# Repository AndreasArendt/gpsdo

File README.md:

# GPSDO

**GPSDO** (GPS Disciplined Oscillator) combines the precision of a high-quality OCXO (Oven-Controlled Crystal Oscillator) with the pulse-per-second (PPS) signal from a GNSS receiver. The goal is to achieve accurate time and frequency reference, down to the nanosecond level.

This project aims to create an **open-source and affordable** GPSDO from scratch, including designing custom hardware (PCB) and developing the supporting software.

# Features
* Combines GNSS PPS with a high-precision OCXO
* Fully open-source hardware and software
* Targeting nanosecond-level timing precision
* Modular design for hardware and software development

# Status
🚧 Under Construction
* The first hardware prototype is currently being tested; all findings are documented in Issue #1
* A Kalman-Filter to estimate `phase`, `frequency_offset` and `frequency_drift` has been implemented
* A PI-Controller is running the GPSDO closed loop
* Flatbuf Messages are implemented to ensure easy-to-extend communication to a host system

# Roadmap
✅ Improve hardware based on findings from V2 prototype  
🔄 Integrate the GNSS receiver on-board for a fully standalone GPSDO  
⚙️ Fine-tune the control loop and filtering algorithms  
📊 Benchmark the true performance against reference standards  

# Contributing
Contributions are welcome! Whether it's hardware design suggestions, software improvements, or analysis scripts, feel free to open an issue or a pull request.

## Compiling flatcc (Windows)
* Navigate into `flatcc` submodule folder.  
* Create `build` folder
* Navigate into `build` folder
* Run `cmake ..`
* Run `cmake --build . --config Release`
* Executable is in `flatcc/bin/Release/flatcc.exe`

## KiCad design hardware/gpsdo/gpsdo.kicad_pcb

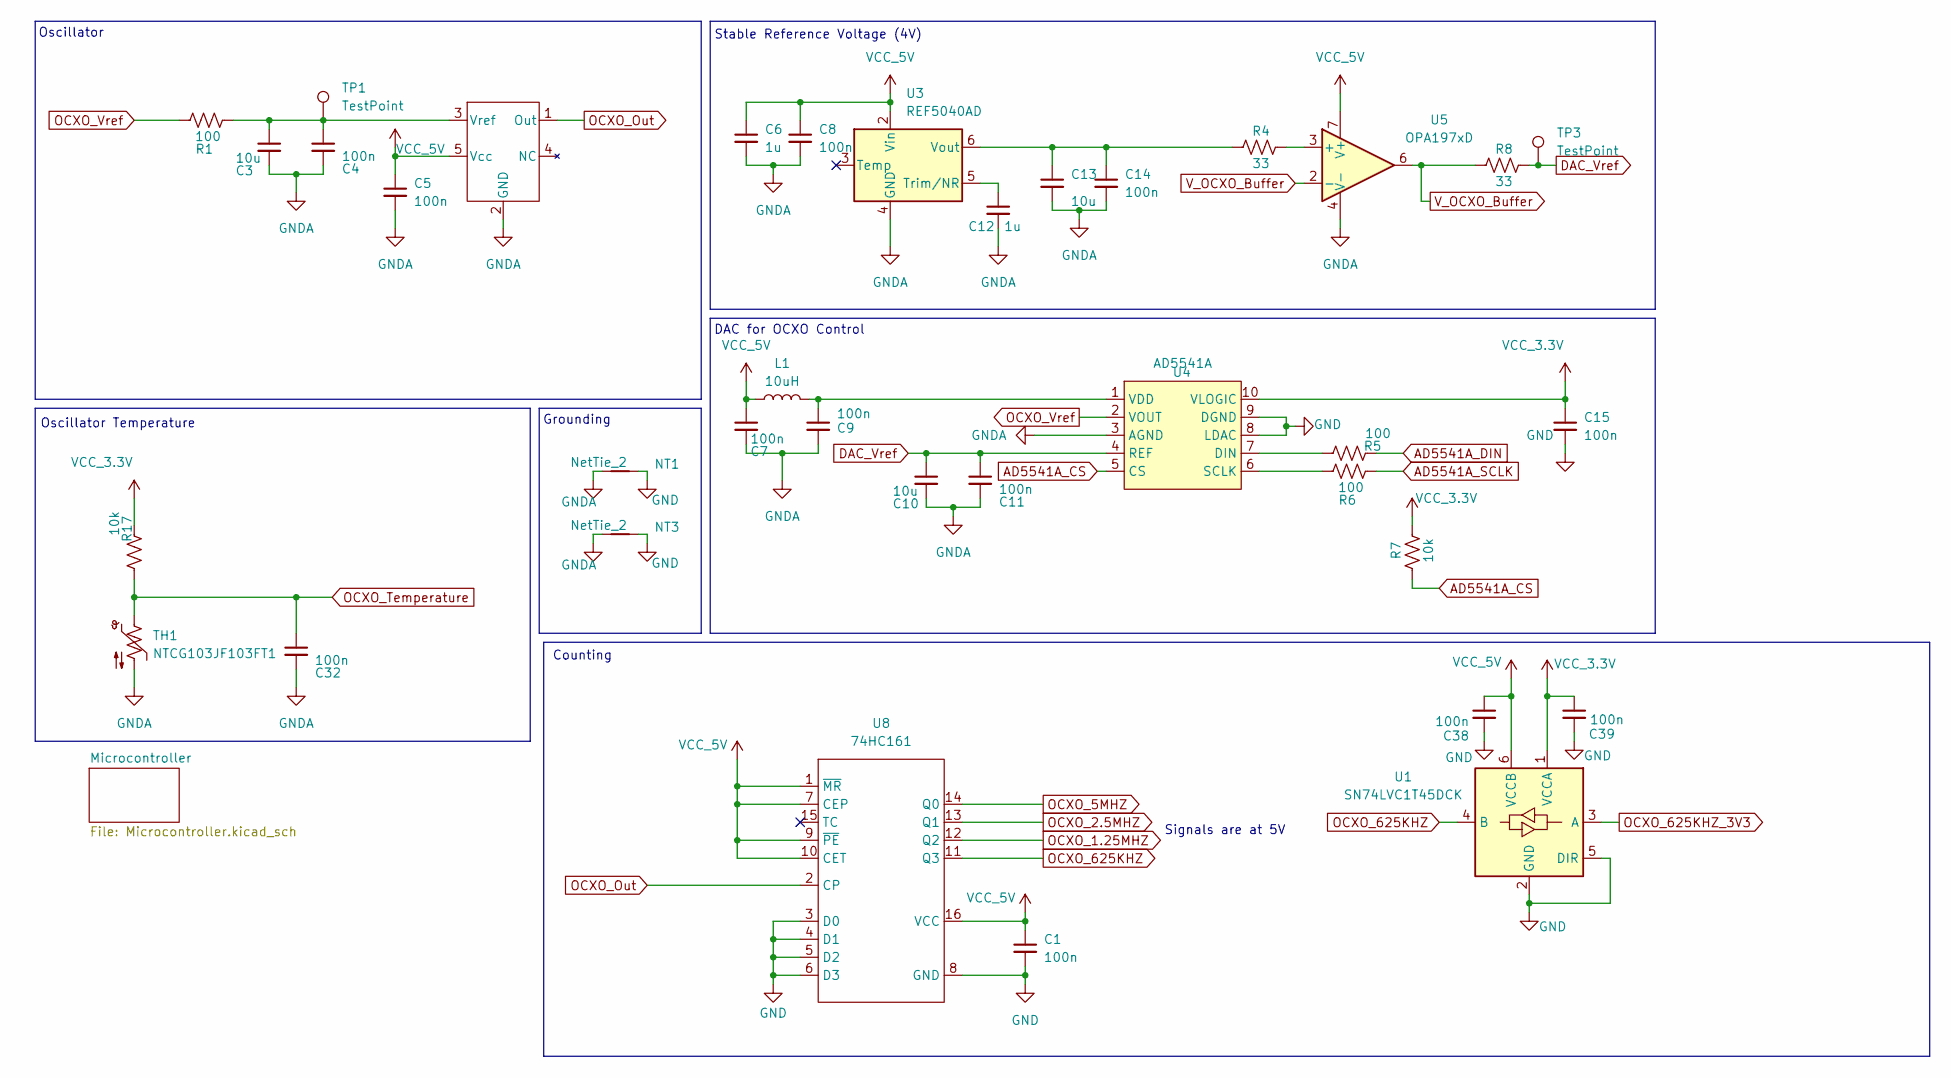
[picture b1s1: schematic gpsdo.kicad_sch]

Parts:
C1, C4, C5, C7, C8, C9, C11, C14, C15, C32, C38, C39: 100n; C_0603_1608Metric; JLC C14663
C3, C10, C13: 10u; C_0603_1608Metric; JLC C19702
C6, C12: 1u; C_0603_1608Metric; JLC C15849
L1: 10uH; L_0603_1608Metric; JLC C1035
NT1, NT3: NetTie_2; NetTie-2_THT_Pad0.3mm
OSC5A2B1: OSC5A2B02
R1, R5, R6: 100; R_0603_1608Metric; JLC C22775
R4, R8: 33; R_0603_1608Metric; JLC C23140
R7, R17: 10k; R_0603_1608Metric; JLC C25804
TH1: NTCG103JF103FT1; R_0603_1608Metric; JLC C209959
TP1, TP3: TestPoint; TestPoint_Pad_D1.5mm
U1: SN74LVC1T45DCK; SOT-363_SC-70-6; JLC C9382
U3: REF5040AD; SOIC-8_3.9x4.9mm_P1.27mm; JLC C1575304
U4: AD5541A; MSOP-10_3x3mm_P0.5mm; JLC C578210
U5: OPA197xD; SOIC-8_3.9x4.9mm_P1.27mm; JLC C79274
U8: 74HC161; SO-16_3.9x9.9mm_P1.27mm; JLC C22436995

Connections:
AD5541A_CS: R7.1, U4.5 (CS); also elsewhere on the board
AD5541A_DIN: R5.2; also elsewhere on the board
AD5541A_SCLK: R6.2; also elsewhere on the board
DAC_Vref: C10.1, C11.1, R8.2, TP3.1, U4.4 (REF)
GND: C1.2, C15.2, C38.2, C39.2, NT1.2, NT3.2, U1.2 (GND), U1.5 (DIR), U4.8 (LDAC), U4.9 (DGND), U8.3 (D0), U8.4 (D1), U8.5 (D2), U8.6 (D3), U8.8 (GND); also elsewhere on the board
GNDA: C3.2, C4.2, C5.2, C6.2, C7.2, C8.2, C9.2, C10.2, C11.2, C12.2, C13.2, C14.2, C32.2, NT1.1, NT3.1, OSC5A2B1.2 (GND), TH1.2, U3.4 (GND), U4.3 (AGND), U5.4 (V-); also elsewhere on the board
unnamed: C3.1, C4.1, OSC5A2B1.3 (Vref), R1.2, TP1.1
unnamed: C12.1, U3.5 (Trim/NR)
unnamed: C13.1, C14.1, R4.1, U3.6 (Vout)
unnamed: R5.1, U4.7 (DIN)
unnamed: R6.1, U4.6 (SCLK)
unnamed: C9.1, L1.2, U4.1 (VDD)
unnamed: R4.2, U5.3 (+)
OCXO_1.25MHZ: U8.12 (Q2); also elsewhere on the board
OCXO_2.5MHZ: U8.13 (Q1); also elsewhere on the board
OCXO_5MHZ: U8.14 (Q0); also elsewhere on the board
OCXO_625KHZ: U1.4 (B), U8.11 (Q3); also elsewhere on the board
OCXO_625KHZ_3V3: U1.3 (A); also elsewhere on the board
OCXO_Out: OSC5A2B1.1 (Out), U8.2 (CP); also elsewhere on the board
OCXO_Temperature: C32.1, R17.1, TH1.1; also elsewhere on the board
OCXO_Vref: R1.1, U4.2 (VOUT); also elsewhere on the board
VCC_5V: C1.1, C5.1, C6.1, C7.1, C8.1, C38.1, L1.1, OSC5A2B1.5 (Vcc), U1.6 (VCCB), U3.2 (Vin), U5.7 (V+), U8.1 (~MR), U8.7 (CEP), U8.9 (~PE), U8.10 (CET), U8.16 (VCC); also elsewhere on the board
VDD_3V3: C15.1, C39.1, R7.2, R17.2, U1.1 (VCCA), U4.10 (VLOGIC); also elsewhere on the board
V_OCXO_Buffer: R8.1, U5.2 (-), U5.6

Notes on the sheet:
Oscillator Temperature
Grounding
Stable Reference Voltage (4V)
Counting
Oscillator
DAC for OCXO Control
Signals are at 5V

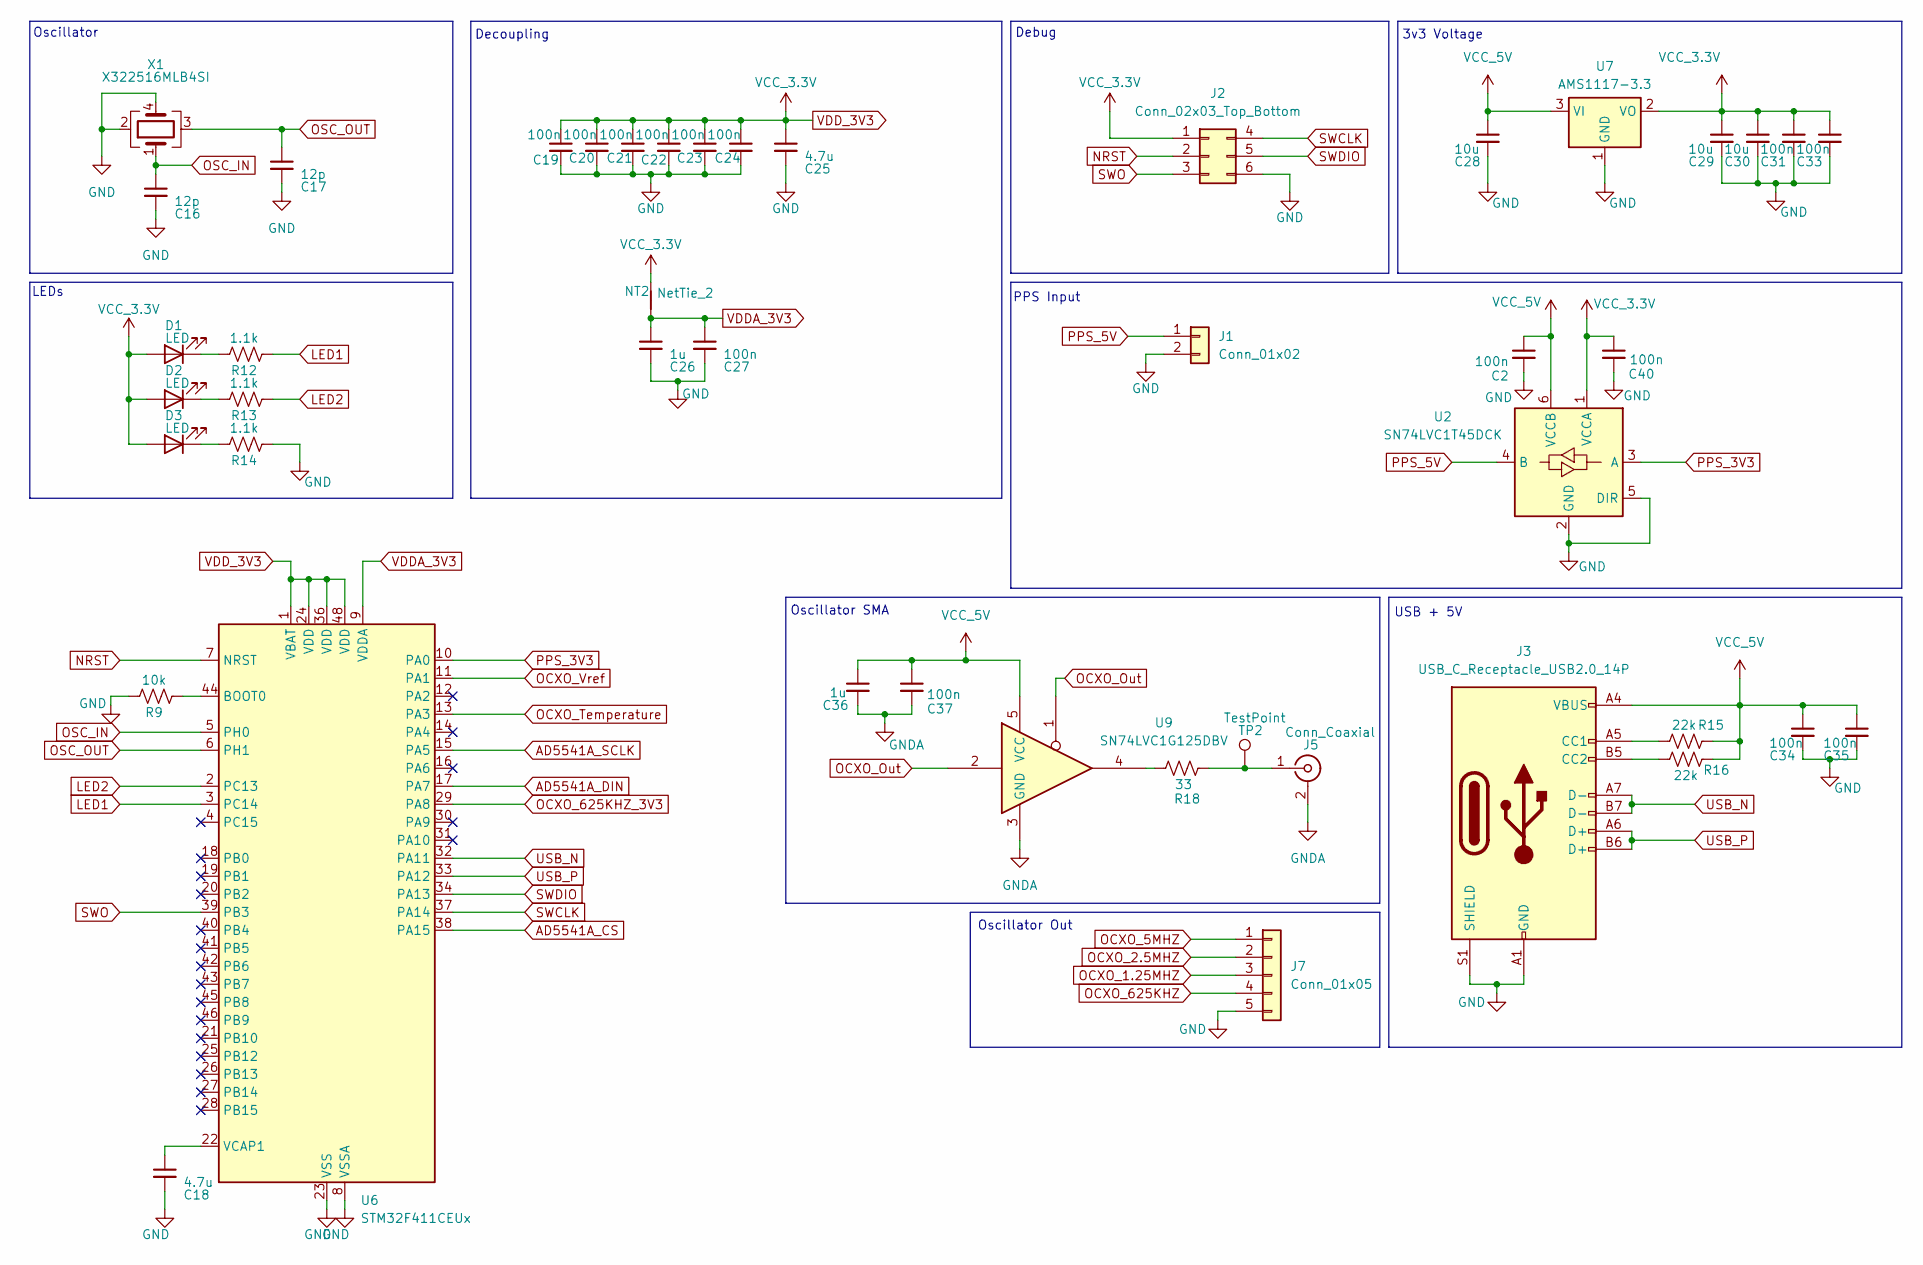
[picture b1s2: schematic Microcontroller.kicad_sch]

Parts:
C2, C19, C20, C21, C22, C23, C24, C27, C31, C33, C34, C35, C37, C40: 100n; C_0603_1608Metric; JLC C14663
C16, C17: 12p; C_0603_1608Metric; JLC C38523
C18, C25: 4.7u; C_0603_1608Metric; JLC C19666
C26, C36: 1u; C_0603_1608Metric; JLC C15849
C28, C29, C30: 10u; C_0603_1608Metric; JLC C19702
D1: LED; LED_0805_2012Metric_Pad1.15x1.40mm_HandSolder; JLC C2296
D2: LED; LED_0805_2012Metric_Pad1.15x1.40mm_HandSolder; JLC C84256
D3: LED; LED_0805_2012Metric_Pad1.15x1.40mm_HandSolder; JLC C2297
J1: Conn_01x02; PinHeader_1x02_P2.54mm_Vertical
J2: Conn_02x03_Top_Bottom; PinHeader_2x03_P2.54mm_Vertical
J3: USB_C_Receptacle_USB2.0_14P; USB_C_Receptacle_G-Switch_GT-USB-7010ASV; JLC C2988369
J5: Conn_Coaxial; SMA_Samtec_SMA-J-P-H-ST-EM1_EdgeMount; JLC C914558
J7: Conn_01x05; PinHeader_1x05_P2.54mm_Vertical
NT2: NetTie_2; NetTie-2_THT_Pad0.3mm
R9: 10k; R_0603_1608Metric; JLC C25804
R12, R13, R14: 1.1k; R_0603_1608Metric; JLC C17375
R15, R16: 22k; R_0603_1608Metric; JLC C31850
R18: 33; R_0603_1608Metric; JLC C23140
TP2: TestPoint; TestPoint_Pad_D1.0mm
U2: SN74LVC1T45DCK; SOT-363_SC-70-6; JLC C9382
U6: STM32F411CEUx; QFN-48-1EP_7x7mm_P0.5mm_EP5.6x5.6mm; JLC C60420
U7: AMS1117-3.3; SOT-223-3_TabPin2; JLC C347222
U9: SN74LVC1G125DBV; SOT-23-5; JLC C23654
X1: X322516MLB4SI; Crystal_SMD_3225-4Pin_3.2x2.5mm; JLC C13738

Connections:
AD5541A_CS: U6.38 (PA15); also elsewhere on the board
AD5541A_DIN: U6.17 (PA7); also elsewhere on the board
AD5541A_SCLK: U6.15 (PA5); also elsewhere on the board
GND: C2.2, C16.2, C17.2, C18.2, C19.2, C20.2, C21.2, C22.2, C23.2, C24.2, C25.2, C26.2, C27.2, C28.2, C29.2, C30.2, C31.2, C33.2, C34.2, C35.2, C40.2, J1.2, J2.6, J3.A1 (GND), J3.A12 (GND), J3.B1 (GND), J3.B12 (GND), J3.S1 (SHIELD), J7.5, R9.2, R14.1, U2.2 (GND), U2.5 (DIR), U6.8 (VSSA), U6.23 (VSS), U6.35 (VSS), U6.47 (VSS), U6.49 (VSS), U7.1 (GND), X1.2, X1.4; also elsewhere on the board
GNDA: C36.2, C37.2, J5.2 (Ext), U9.3 (GND); also elsewhere on the board
LED1: R12.1, U6.3 (PC14)
LED2: R13.1, U6.2 (PC13)
NRST: J2.2, U6.7 (NRST)
unnamed: D1.1 (K), R12.2
unnamed: D2.1 (K), R13.2
unnamed: D3.1 (K), R14.2
unnamed: J3.A5 (CC1), R15.2
unnamed: J3.B5 (CC2), R16.2
unnamed: J5.1 (In), R18.1, TP2.1
unnamed: R18.2, U9.4
unnamed: R9.1, U6.44 (BOOT0)
unnamed: C18.1, U6.22 (VCAP1)
OCXO_1.25MHZ: J7.3; also elsewhere on the board
OCXO_2.5MHZ: J7.2; also elsewhere on the board
OCXO_5MHZ: J7.1; also elsewhere on the board
OCXO_625KHZ: J7.4; also elsewhere on the board
OCXO_625KHZ_3V3: U6.29 (PA8); also elsewhere on the board
OCXO_Out: U9.1, U9.2; also elsewhere on the board
OCXO_Temperature: U6.13 (PA3); also elsewhere on the board
OCXO_Vref: U6.11 (PA1); also elsewhere on the board
OSC_IN: C16.1, U6.5 (PH0), X1.1
OSC_OUT: C17.1, U6.6 (PH1), X1.3
PPS_3V3: U2.3 (A), U6.10 (PA0)
PPS_5V: J1.1, U2.4 (B)
SWCLK: J2.4, U6.37 (PA14)
SWDIO: J2.5, U6.34 (PA13)
SWO: J2.3, U6.39 (PB3)
USB_N: J3.A7 (D-), J3.B7 (D-), U6.32 (PA11)
USB_P: J3.A6 (D+), J3.B6 (D+), U6.33 (PA12)
VCC_5V: C2.1, C28.1, C34.1, C35.1, C36.1, C37.1, J3.A4 (VBUS), J3.A9 (VBUS), J3.B4 (VBUS), J3.B9 (VBUS), R15.1, R16.1, U2.6 (VCCB), U7.3 (VI), U9.5 (VCC); also elsewhere on the board
VDDA_3V3: C26.1, C27.1, NT2.1, U6.9 (VDDA)
VDD_3V3: C19.1, C20.1, C21.1, C22.1, C23.1, C24.1, C25.1, C29.1, C30.1, C31.1, C33.1, C40.1, D1.2 (A), D2.2 (A), D3.2 (A), J2.1, NT2.2, U2.1 (VCCA), U6.1 (VBAT), U6.24 (VDD), U6.36 (VDD), U6.48 (VDD), U7.2 (VO); also elsewhere on the board

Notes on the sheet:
Oscillator Out
Debug
PPS Input
LEDs
USB + 5V
Oscillator SMA
Decoupling
3v3 Voltage
Oscillator

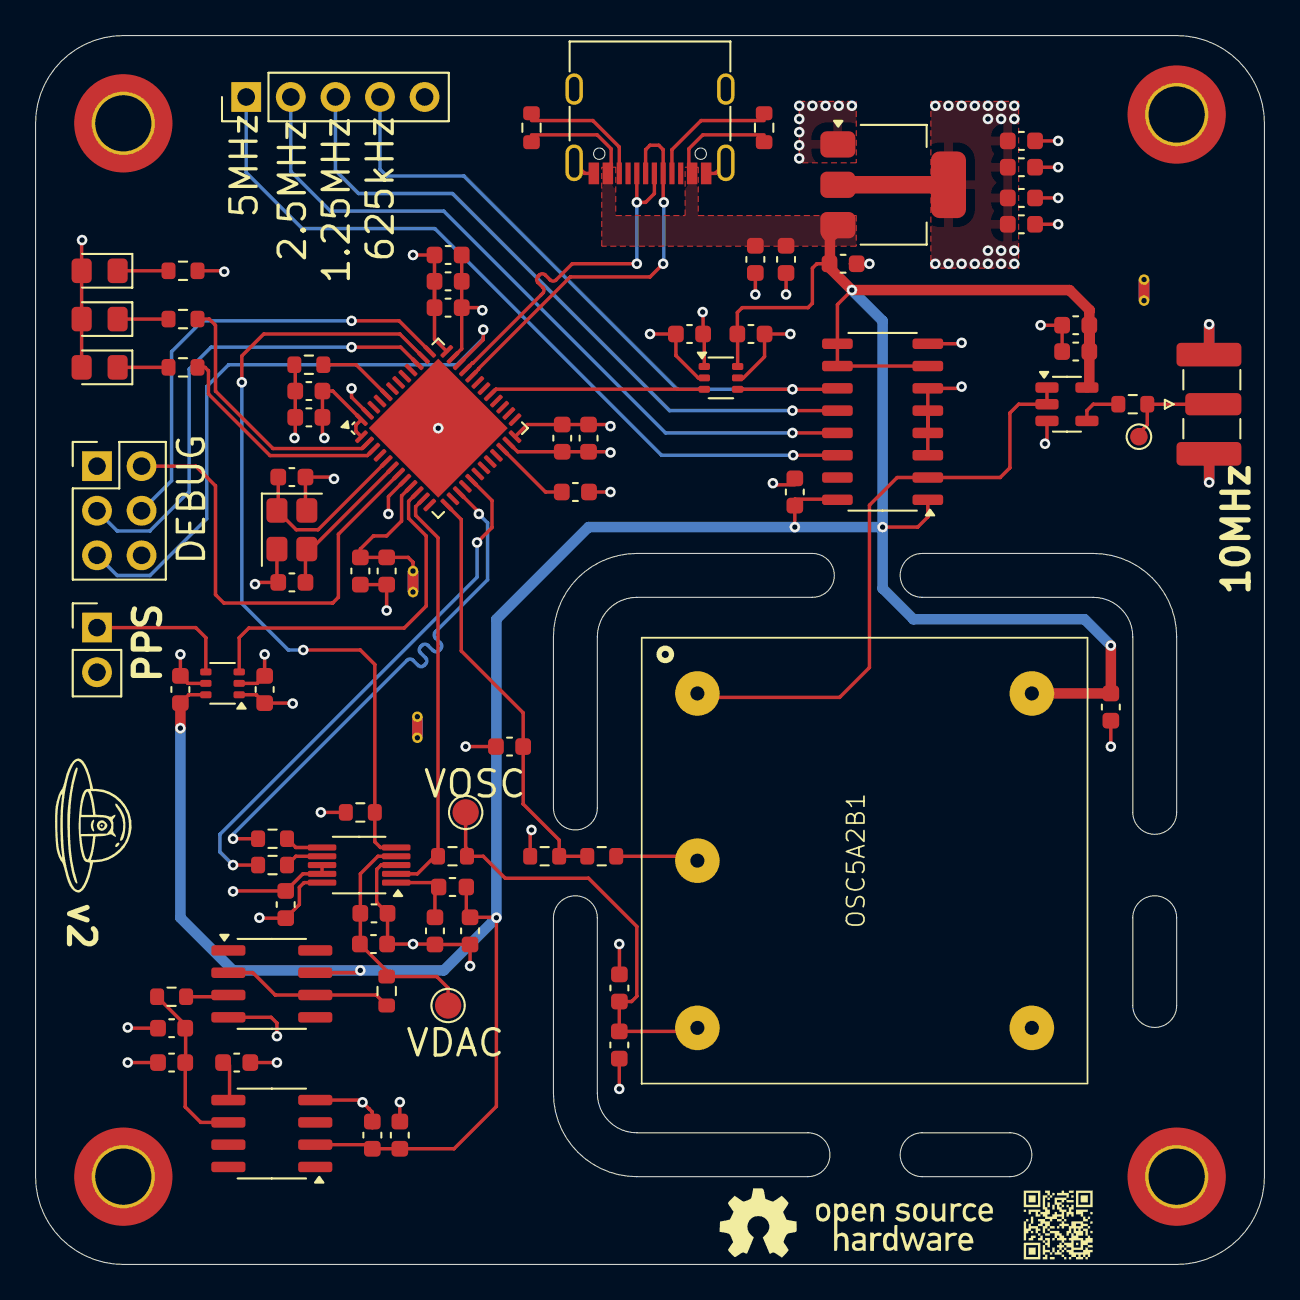
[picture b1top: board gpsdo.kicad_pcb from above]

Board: 4 copper layers, 70.0 x 70.0 mm, 81 parts (0 on the bottom side), 46 nets.

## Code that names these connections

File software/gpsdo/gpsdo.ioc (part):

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Mcu.Name=STM32F411C(C-E)Ux
Mcu.Package=UFQFPN48
Mcu.UserName=STM32F411CEUx
PA0-WKUP.Signal=S_TIM5_CH1
PA1.Signal=ADCx_IN1
PA11.Mode=Device_Only
PA11.Signal=USB_OTG_FS_DM
PA12.Mode=Device_Only
PA12.Signal=USB_OTG_FS_DP
PA13.Mode=Serial_Wire
PA13.Signal=SYS_JTMS-SWDIO
PA14.Mode=Serial_Wire
PA14.Signal=SYS_JTCK-SWCLK
PA15.Signal=GPIO_Output
PA3.Signal=ADCx_IN3
PA5.Mode=TX_Only_Simplex_Unidirect_Master
PA5.Signal=SPI1_SCK
PA7.Mode=TX_Only_Simplex_Unidirect_Master
PA7.Signal=SPI1_MOSI
PA8.Signal=S_TIM1_CH1
PB3.Signal=SYS_JTDO-SWO
PC13-ANTI_TAMP.Signal=GPIO_Output
PC14-OSC32_IN.Signal=GPIO_Output
PH0\ -\ OSC_IN.Mode=HSE-External-Oscillator
PH0\ -\ OSC_IN.Signal=RCC_OSC_IN
PH1\ -\ OSC_OUT.Mode=HSE-External-Oscillator
PH1\ -\ OSC_OUT.Signal=RCC_OSC_OUT
RCC.HSE_VALUE=16000000
RCC.SYSCLKFreq_VALUE=96000000
RCC.SYSCLKSource=RCC_SYSCLKSOURCE_PLLCLK
board=custom

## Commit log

2025-09-03 update clock configuration
2025-09-03 set TIM1 and TIM2 for input capture
2025-09-03 re-configuring TIM1 and enabling USB - lowering clock frequency
2025-09-06 starting pcb
2025-09-07 add i2c for ad5639; generate sine
2025-09-07 add freertos
2025-09-07 update sine software part
2025-09-07 update hardware
2025-09-09 update schematics
2025-09-09 cleanup schematics
2025-09-29 update pcb; update hal
2025-09-30 update hal; update schematics and routing
2025-10-01 update routing
2025-10-01 add symbols to pcb
2025-10-01 cleanup pcb
2025-10-01 add qr code
2025-10-01 bugfixing and fine tuning
2025-10-01 cleanup
2025-10-01 final changes
2025-10-01 cleanup; remove references from silkscreen
2025-10-01 update pcb
2025-10-01 create first prod files
2025-10-02 final ratsnest
2025-10-02 update routing; bugfix in downsampling; replace voltage dividers with level shifter
2025-10-02 update layout
2025-10-02 bugfix in bom
2025-10-02 version 1 put into production
2025-10-04 revisit footprints
2025-10-17 configuration to count pulses between pps
2025-10-18 enable usb
2025-10-18 starting refactoring code
2025-10-18 add debug output
2025-10-19 add missing include
2025-10-19 add kalman filter for frequency error and frequency error drift estimation
2025-10-19 update gitignore
2025-10-25 change clock to 16mhz
2025-10-25 rework usb with queue for sending from any task
2025-10-25 implementation of adc
2025-10-27 fix spi; voltage setting not working exactly, but close
2025-10-28 fix spi mode
2025-10-28 Implementation of leds
2025-10-28 implement led blinking with pps
2025-10-28 cleanup kf
2025-10-29 add possibility to postprocess kalman filter
2025-10-29 re-tune kalman filter; adjust postprocessing
2025-10-29 kalman filter tweaking
2025-11-04 implementation of usb receive function
2025-11-07 prepare allan variance plot
2025-11-08 rework usb driver; add kalman filter
2025-11-08 cleanup, disable driver, add logging for stack overflows
2025-11-08 add license
2025-11-08 add sanity checking for filter value
2025-11-08 cleanup filter; add exponential smoothing
2025-11-08 first version of closed loop system
2025-11-08 update controller
2025-11-08 add live plotting
2025-11-08 cleanup timer isr
2025-11-08 update plotting
2025-11-08 adjust jitter filter; always output data for debugging
2025-11-09 add flatcc submodule
2025-11-09 #3 add flatbuffer to embedded code
2025-11-09 #3 start working on python flatbuf
2025-11-09 #3 first end-to-end version
2025-11-09 #3 fully working end-to-end
2025-11-09 setup plotting again
2025-11-09 adjust tuning
2025-11-10 bugfix in controller
2025-11-10 writing csv files
2025-11-12 disable control; update postprocessing scripts
2025-11-12 strip down pp kalman filter
2025-11-12 extend kalman filter to three states
2025-11-13 rewrite kalman filter - fixes #6
2025-11-13 update filter
2025-11-13 diable controller
2025-11-22 update python tooling
2025-11-22 fix tooling
2025-11-22 align filter on python and c code side
2025-11-22 closed loop operation; update gitignore
2025-11-22 adjust schemat to have kf debug
2025-11-22 refactoring python side
2025-11-23 increase heap and stack sizes dramatically
2025-11-23 calling free on flatbufs to prevent mheap overflow
2025-11-23 retune pid; adjust postprocessing scripts
2025-11-23 switch towards full static flatbuf implementation; reduce heap memory; update controller; add ema smoothing
2025-11-25 correct allandev computation
